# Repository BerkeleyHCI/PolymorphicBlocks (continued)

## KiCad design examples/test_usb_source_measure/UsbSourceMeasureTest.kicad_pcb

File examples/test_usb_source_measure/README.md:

First unit:
- J1: Molex 217179-0001
- J2: GCT USB4105-GF-A
- High side transistor: ~NPN PHPT60410NYX~, NMOS SIR172ADP-T1-GE3
- Low side transistor: ~PNP PHPT60410PYX (exploded at ~3A)~, PMOS SQJ433EP-T1_GE3

Second unit:
- D1, D2: white LEDs
- U15, U16: CPC1106N
- U20, U14, U18 (HV opamp): MC33171DT
- U4, U6, U8, U10, U12: MCP6001T-I/OT

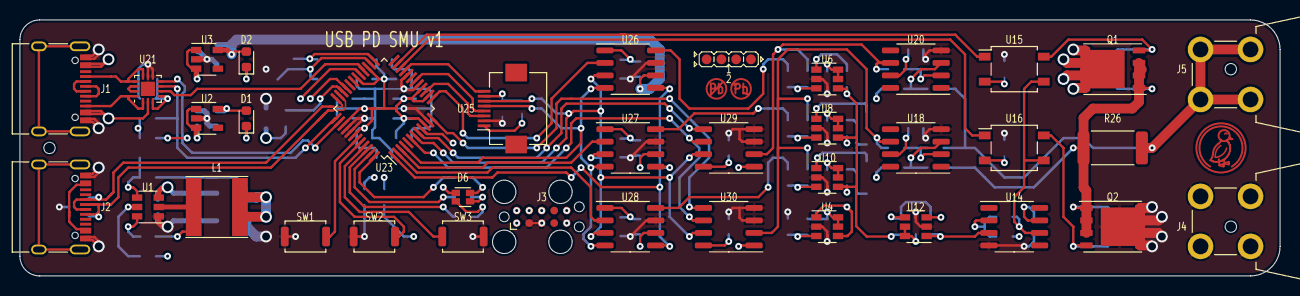
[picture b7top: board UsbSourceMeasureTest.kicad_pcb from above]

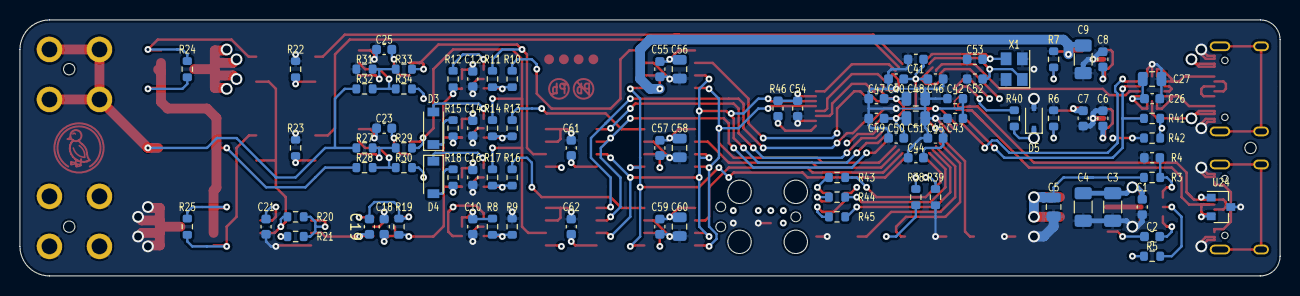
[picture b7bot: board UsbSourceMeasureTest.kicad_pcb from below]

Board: 4 copper layers, 128.0 x 26.0 mm, 130 parts (88 on the bottom side), 82 nets.

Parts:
1: LeadFree; Indicator_LeadFree
2: IdDots4; Indicator_IdDots_4
3, 4, 5: JlcToolingHole_1.152mm
C1, C2, C10, C12, C14, C16, C18, C21, C23, C25, C26, C40, C42, C44, C46, C47, C49, C50, C55, C57, C59: CC0603KRX7R9BB104 (YAGEO) - X7R 100nF ±10% 50V 06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; C_0603_1608Metric
C3, C4: CL31A106KBHNNNE (Samsung Electro-Mechanics) - X5R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; C_1206_3216Metric
C5, C27, C48, C51, C56, C58, C60: CL21A106KAYNNNE (Samsung Electro-Mechanics) - X5R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; C_0805_2012Metric
C6, C7, C8, C54, C61, C62: CL10A105KB8NNNC (Samsung Electro-Mechanics) - X5R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; C_0603_1608Metric
C9: CL31B225KBHNNNE (Samsung Electro-Mechanics) - X7R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; C_1206_3216Metric
C19: 1nF; C_0603_1608Metric
C41, C43, C45: 0603B103K500NT (FH(Guangdong Fenghua Advanced Tec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; C_0603_1608Metric
C52, C53: CL10C100JB8NNNC (Samsung Electro-Mechanics) - C0G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; C_0603_1608Metric
D1, D2: LED; LED_0603_1608Metric
D3, D4: DSS14UTR (SMC Diode Solutions) - Vr=40V, I=1A; D_SOD-123
D5: DDZ3V6ASF-7 (Diodes Incorporated) - Vz=3.57V, I=9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; D_SOD-323
D6: EAST1616RGBB2 (Everlight Electronics Co Ltd); LED_LiteOn_LTST-C19HE1WT
J1, J2: COM-15111 (Sparkfun); USB_C_Receptacle_XKB_U262-16XN-4BVC11
J3: SWD; Tag-Connect_TC2050-IDC-FP_2x05_P1.27mm_Vertical
J4, J5: CT3151-* (CalTest); CalTest_CT3151
L1: NR6028T470M (Taiyo Yuden) - 47µH, 920mA; L_Taiyo-Yuden_NR-60xx
Q1: SIR172ADP-T1-GE3 (Vishay Siliconix) - Vds=30 V, I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; PowerPAK_SO-8_Single
Q2: SQJ433EP-T1_GE3 (Vishay Siliconix) - Vds=30 V, Id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; PowerPAK_SO-8_Single
R3: 0603WAF1102T5E (UNI-ROYAL(Uniroyal Elec)) - 11kΩ 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; R_0603_1608Metric
R4: 0603WAF1501T5E (UNI-ROYAL(Uniroyal Elec)) - 1.5kΩ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; R_0603_1608Metric
R5: 0603WAF5103T5E (UNI-ROYAL(Uniroyal Elec)) - ±1% 5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; R_0603_1608Metric
R6, R7, R43, R44, R45: 0603WAF6800T5E (UNI-ROYAL(Uniroyal Elec)) - 680Ω 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; R_0603_1608Metric
R8, R9: 0603WAF1003T5E (UNI-ROYAL(Uniroyal Elec)) - ±1% 1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; R_0603_1608Metric
R10, R11, R13, R14, R16, R17, R27, R28, R29, R30, R33, R34, R40: 0603WAF1002T5E (UNI-ROYAL(Uniroyal Elec)) - ±1% ±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; R_0603_1608Metric
R12, R19, R24, R25, R41, R42: 0603WAF4701T5E (UNI-ROYAL(Uniroyal Elec)) - ±1% 4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; R_0603_1608Metric
R15, R18: 0603WAF100KT5E (UNI-ROYAL(Uniroyal Elec)) - ±1% ±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; R_0603_1608Metric
R20: 0603WAF3902T5E (UNI-ROYAL(Uniroyal Elec)) - ±1% 3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; R_0603_1608Metric
R21: 0603WAF2001T5E (UNI-ROYAL(Uniroyal Elec)) - ±1% 2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; R_0603_1608Metric
R22, R23: 0603WAF1600T5E (UNI-ROYAL(Uniroyal Elec)) - ±1% ±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; R_0603_1608Metric
R26: 100m, 1%, 1.0 W; R_2512_6332Metric
R31, R32: 0603WAF2203T5E (UNI-ROYAL(Uniroyal Elec)) - ±1% ±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; R_0603_1608Metric
R38, R39: 0603WAF1502T5E (UNI-ROYAL(Uniroyal Elec)) - ±1% 1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; R_0603_1608Metric
R46: 0603WAF1000T5E (UNI-ROYAL(Uniroyal Elec)) - ±1% ±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; R_0603_1608Metric
SW1, SW2, SW3: 3.9x2.9mm Switch; SW_Push_SPST_NO_Alps_SKRK
U1: TPS54202H (Texas Instruments); SOT-23-6
U2: XC6209F332MR-G (Torex Semiconductor Ltd); SOT-23-5
U3: AP2210K-3.0 (Torex Semiconductor Ltd); SOT-23-5
U4, U6, U8, U10, U12: TLV9061SQDBVRQ1 (Texas Instruments); SOT-23-6
U14, U18, U20: OPA197IDR (Texas Instruments); SO-8_3.9x4.9mm_P1.27mm
U15, U16: G3VM-61GR2 (Omron Electronics); SO-4_4.4x4.3mm_P2.54mm
U21: FUSB302B11MPX (ON Semiconductor); WQFN-14-1EP_2.5x2.5mm_P0.5mm_EP1.45x1.45mm
U23: LPC1549JBD48 (NXP); LQFP-48_7x7mm_P0.5mm
U24: TPD2E009 (Texas Instruments); SOT-23
U25: QT096T_IF09, FH12-8S-0.5SH(55); Hirose_FH12-8S-0.5SH_1x08-1MP_P0.50mm_Horizontal
U26, U27, U28: MCP4921-E/SN (Microchip Technology); SO-8_3.9x4.9mm_P1.27mm
U29, U30: MCP3201T-BI/SN (Microchip Technology); SO-8_3.9x4.9mm_P1.27mm
U31: Duck; Symbol_Duckling
X1: ABM8G-106-12.000MHZ-T (Abracon LLC) - 12MHz, 10pF; Oscillator_SMD_Abracon_ASE-4Pin_3.2x2.5mm

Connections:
adc_i_cs_net: U23.12, U30.5
adc_v.vin: R11.1, R33.1, U20.6, U29.2
adc_v_cs_net: U23.8, U29.5
control.amp.input: C19.1, U12.1, U14.3
control.amp.r2.a: R20.2, R21.1, U14.2
control.control_current_source: R13.1, U27.8
control.control_voltage: R10.1, U26.8
control.driver.(adapter)high_res.b.src: Q1.4, R24.2, U15.4
control.driver.control: R20.1, U14.6, U15.3, U16.3
control.driver.high_gate.ic.ledk: R22.1, U15.2
control.driver.low_gate.apull: Q2.4, R25.2, U16.4
control.driver.low_gate.ic.ledk: R23.1, U16.2
control.driver.out: Q1.1, Q1.2, Q1.3, Q2.1, Q2.2, Q2.3, R24.1, R25.1, R26.1, R28.1
control.err_sink.(adapter)diode.anode.src: D4.2, R18.1
control.err_sink.(adapter)diode.cathode.dst: D4.1, U10.1
control.err_sink.(adapter)rbot.b.dst: R16.2, R17.2, U10.3
control.err_source.(adapter)rout.a.dst: D3.1, R15.1
control.err_source.diode.anode: D3.2, U8.1
control.err_source.rtop.b: R13.2, R14.2, U8.3
control.err_volt.(adapter)rout.a.dst: R12.1, U6.1
control.err_volt.amp.inp: R10.2, R11.2, U6.3
control.imeas.(adapter)r2.b.dst: R28.2, R30.2, U18.3
control.imeas.(adapter)rf.b.dst: R27.2, R29.2, U18.2
control.int.(adapter)r.b.dst: C19.2, R19.2, U12.4
control.int_link: R12.2, R15.2, R18.2, R19.1, U6.4, U8.4, U10.4
control.measured_current: R14.1, R17.1, R29.1, U18.6, U30.2
control.vmeas.r2.b: R32.2, R34.2, U20.3
control.vmeas.rf.b: R31.2, R33.2, U20.2
crystal.crystal.a: C52.1, U23.26, X1.1
dac_in.out: R16.1, U28.8
dac_in_cs_net: U23.2, U28.2
dac_ip_cs_net: U23.3, U27.2
dac_ldac_net: U23.1, U26.5, U27.5, U28.5
dac_v_cs_net: U23.13, U26.2
data_usb.B4: J2.A4, J2.A9, J2.B4, J2.B9
gnd: C1.2, C3.2, C4.2, C5.2, C6.2, C7.2, C8.2, C9.2, C10.2, C12.2, C14.2, C16.2, C18.2, C21.2, C23.2, C25.2, C26.2, C27.2, C40.2, C41.2, C42.2, C43.2, C44.2, C45.2, C46.2, C47.2, C48.2, C49.2, C50.2, C51.2, C52.2, C53.2, C54.2, C55.2, C56.2, C57.2, C58.2, C59.2, C60.2, C61.2, C62.2, D5.2, J1.A1, J1.A12, J1.B1, J1.B12, J2.A1, J2.A12, J2.B1, J2.B12, J3.2, J3.3, J3.5, J4.1, Q2.5, R4.2, R6.2, R7.2, R9.2, R22.2, R23.2, R31.1, R39.1, SW1.1, SW2.1, SW3.1, U1.1, U2.2, U3.2, U4.2, U6.2, U8.2, U10.2, U12.2, U14.4, U18.4, U20.4, U21.8, U21.9, U21.15, U23.11, U23.17, U23.20, U23.40, U23.41, U24.3, U25.2, U26.7, U27.7, U28.7, U29.3, U29.4, U30.3, U30.4, X1.2, X1.4
high_en_net: U15.1, U23.23
i2c_pull.i2c.sda: R42.2, U21.7, U23.38
lcd.device.leda: R46.2, U25.1
lcd_cs_net: U23.21, U25.8
lcd_reset_net: U23.15, U25.3
lcd_rs_net: U23.18, U25.4
led_3v3.res.a: D1.1, R6.1
led_analog.package.k: D2.1, R7.1
low_en_net: U16.1, U23.22
mcu.i2c_0.scl: R41.2, U21.6, U23.37
mcu.swd.reset: J3.6, R40.2, U23.34
mcu.swd.swdio: J3.10, R38.2, U23.33
mcu.swd.swo: J3.8, U23.9
mcu.usb_0.dp: J2.A6, J2.B6, U23.35, U24.2
mcu.xtal.xtal_out: C53.1, U23.25, X1.3
outp.port: J5.1, R26.2, R27.1, R32.1
pd.cc.cc2: J1.B5, U21.1, U21.14
pd.ic.vconn: U21.12, U21.13
pd_int_net: U21.5, U23.28
pwr_usb.cc.cc1: J1.A5, U21.10, U21.11
pwr_usb.usb.dm: J1.A7, J1.B7
pwr_usb.usb.dp: J1.A6, J1.B6
ref_div.center: R8.2, R9.1, U4.3
reg_5v.(adapter)boot_cap.pos.dst: C2.1, U1.6
reg_5v._pwr_out_net: C5.1, C6.1, C8.1, L1.2, R3.1, U2.1, U2.3, U3.1, U3.3
reg_5v._switch_net: C2.2, L1.1, U1.2
reg_5v.en_res.b: R5.2, U1.5
reg_5v.ic.fb: R3.2, R4.1, U1.4
rgb.green_res.a: D6.4, R44.1
rgb.package.k_blue: D6.1, R45.1
rgb.package.k_red: D6.3, R43.1
rgb_b_net: R45.2, U23.46
rgb_g_net: R44.2, U23.47
rgb_r_net: R43.2, U23.48
spi_net.miso: U23.6, U29.6, U30.6
spi_net.mosi: U23.4, U25.5, U26.4, U27.4, U28.4
spi_net.sck: U23.7, U25.6, U26.3, U27.3, U28.3, U29.7, U30.7
sw1_chain_0: SW1.2, U23.43
sw2_chain_0: SW2.2, U23.44
sw3_chain_0: SW3.2, U23.45
swd.swd.swclk: J3.9, R39.2, U23.29
usb_esd.usb.dm: J2.A7, J2.B7, U23.36, U24.1
v3v3: C7.1, C12.1, C14.1, C16.1, C18.1, C26.1, C27.1, C40.1, C41.1, C42.1, C43.1, C44.1, C45.1, C46.1, C47.1, C48.1, C49.1, C50.1, C51.1, C54.1, C55.1, C56.1, C57.1, C58.1, C59.1, C60.1, C61.1, C62.1, D1.2, D5.1, D6.2, J3.1, R38.1, R40.1, R41.1, R42.1, R46.1, U2.5, U6.5, U6.6, U8.5, U8.6, U10.5, U10.6, U12.5, U12.6, U21.3, U21.4, U23.10, U23.14, U23.16, U23.27, U23.30, U23.39, U23.42, U25.7, U26.1, U27.1, U28.1, U29.8, U30.8
vanalog: C9.1, C10.1, D2.2, R8.1, U3.5, U4.5, U4.6, U26.6, U27.6, U28.6, U29.1, U30.1
vcenter: R21.2, R30.1, R34.1, U4.1, U4.4, U12.3
vusb: C1.1, C3.1, C4.1, C21.1, C23.1, C25.1, J1.A4, J1.A9, J1.B4, J1.B9, Q1.5, R5.1, U1.3, U14.7, U18.7, U20.7, U21.2
